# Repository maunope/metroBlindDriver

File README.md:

# Disclaimer
This is still a prototype; the circuit design was built and tested on a perfboard, the KiCad board design was never tested. Use at your own risk and plz **don't come whining if you damage stuff or set your house on fire.**

# WARNING
This project entails working with a 220V powered device with a metal chassis and **no grounding**. These devices are 40+ years old and saw lots of abuse; wire insulation may fail, and motor windings may short circuit. Before wiring anything up, check impedance between the chassis, the engine hull, and all contacts carrying 220V power; anything below 2 megaohms means insulation needs to be re-checked. 
Consider wiring the blind chassis to the ground line for additional safety.

# Metro Blinds Driver

Arduino-based driver board to control Acotral MA100 electric locomotives' front and side stops blinds.

Acotral MA100s were first issued to Rome's **"A"** metro line where they were in service between 1980 and 2005, before being overhauled/modified and reassigned to the Roma Lido line until their decommissioning in 2018. 

[Trasporti di Roma](https://romaatac.altervista.org/mezzi-di-roma/ma-100/)
[Wikipedia](https://it.wikipedia.org/wiki/Elettromotrici_ACOTRAL_MA_100)

Stops signaling blinds coming from wagon dismantling started circulating among flip clock collectors and have become a somewhat common find on online marketplaces.

Blinds are controlled through a 7-bit string identifying stops and are powered at 110V AC (motor) / 48V DC (control). This project emulates original locomotive control signals to drive them and display stops.

The board design in this project runs 5V DC control signals and 220V power; it requires minimal modifications to the original blinds' wiring. It is fairly easy, however, to adapt it to run 48V/110V to 100% preserve the integrity of the original wiring.

## Main features   
- Runs through stops using the blind's internal motor
- Allows manual stop selection or programmed stops sequence mode
- Allows saving configurations to the Arduino EEPROM
- Implements several controls to prevent damage/overheating in case of malfunctions

## Lateral blind design
The `LATERAL_BLIND` compile flag enables a command table built for smaller punched rollers found on side-mounted train blinds. This mode is intended to address blinds with smaller punched rollers, those mounted on the side of trains rather than the larger frontal rollers.

On the specimen I tested, the pinout was different compared to the larger frontal roller, but this may not always be true. If your roller is different, you may need to recreate the command array for your exact roller.

## Manual vs. Program mode

In **manual mode** (default), stops are selected through serial port commands or single button presses. The board LED is lit during Manual mode. 

**Program mode** automatically loops a sequence of stops, one step every hour by default. The program will be resumed from the last reached stop in case of power OFF/ON; the hourly step timer will be reset. The board LED is off during Program mode.

To switch between modes, either use serial commands or press the board button for **3 seconds**. 

## Dependencies

- EEPROM (comes with Arduino IDE)
- [Rocket Scream Low Power](https://github.com/rocketscream/Low-Power)

## Arduino circuit board

Check the schematic in this repo; I've built and tested it on perfboard. The board design might not be 100% correct, and the layout could definitely use some improvement.

**How to read LED signals**

Either for good or bad news, the Arduino board LED will flash. 

## Original electromechanical control logic 

A punched roller is used to encode 40 unique blind positions. When a string of bits is applied to the pinstripe, the motor spins until the holes combination under the pinstripe matches powered pins, i.e.:

- **0b00111000** bit string corresponding to Termini station is applied to the pinstripe, powering pins 4, 5, 6 from the left (1st left pin is common)
- **0b0011110** bit string on the control roller is under the pinstripe; current flows through pins 4, 5, 6, and the motor spins
- Next roller bit string is **0b0100110** on the control roller; current flows through pin 6, and the motor keeps spinning
- The roller bit string is now **0b11000111**; all 1s on the pinstripe match a 0 on the roller, no current flows, the motor **stops** and will remain still until a different bit string is selected.

The original control board has 7 control pins, 2 relay coil pins, and 2 motor power pins, exposed through a DIN 41622 male connector on the side or back panel.

The original wiring:
- Pin 1-6 and 12: stop selection bit string
- Pin 11: unwired
- Pin 10: 110V AC to relay interrupted line
- Pin 9: Relay coil (+48V signal from selection roller return line)
- Pin 8: Relay coil N
- Pin 7: 110V returning from motor

## Blind Board schematic and modifications

The blind board schematic is available in "metroBlindDriver blind board" KiCad design:

In the original blind design, 48V DC bits would be fed into pins 1-6 and 12; they would reach the control roller through diodes and would power the 48V relay coil through the roller common pin until the desired stop was reached. 

The original blind wiring can be easily modified to accept standard household 220V AC power and 5V DC signals.

**IMPORTANT**: Don't use this board design with 48V signals to avoid damage and fire hazard!

**IMPORTANT**: Don't run 220V AC through the motor before its coils are wired in series to avoid damage and fire hazard!

**220V AC motor wiring** Wire the motor as shown in the picture below to drive it with 220V AC power. Plastic motor caps on most (all?) blinds have diagrams explaining how to wire coils in series/parallel.

**5V DC external relay wiring**

To bypass the 48V coil and use an external relay, clip the motor **N** wire from the connector board trace (board end, not motor end!) and solder it to the top left pin on the DIN connector. If in doubt, use the only pin trace with no wires attached. 

Replacing the original 48V relay with a 5V or 12V one isn't sufficient, as the coil has a 4kohm resistor wired in series; plus, compatible relays are out of production, hard to source, and quite expensive. 

I wanted to preserve the original circuitry as much as possible, but definitely didn't want to faff with 48V signals.
I figured since I had already wired the motor for 220V AC, another small modification wouldn't matter much, and moving a wire to a different pin seemed way less invasive than replacing a relay and a big *ss resistor.
You might want to do things differently here; the circuit is easy enough to work with, these are just my 2c :-) 

Rewired schematic below:

The new wiring:
- Pin 1-6 and 12: 5V bit string
- Pin 11: to motor relay NO contact on Arduino board
- Pin 10: unwired, can be used to ground the blind chassis
- Pin 9: to Arduino "Any Running" pin
- Pin 8: unwired
- Pin 7: to motor relay NO contact on Arduino board

## How to install and adjust

**First things first, let's not fry stuff**

- Check wirings and voltages
- **Mandatory**: rewire the blind board to use an external 5V relay; **don't use 48V signals with this Arduino board design!**
- **Optional**: rewire the motor to run on 220V AC; if you happen to have a 110V AC power source, that will work fine
- Wire the DIN connector pins; be sure not to short circuit anything
- Power the board and the motor **L** wire
 **No smoke? Good.**

By default, the controller will wait for commands in manual mode with the board LED **ON**.

- Press the board button briefly; the blind should roll one stop forward
- (Optional) press the board button for 3 seconds to switch to Program mode

## Push buttons commands

- **Brief press:** move one stop forward
- **3 seconds press:** switch between Manual and Program mode

## Serial port commands

Commands format: **(<<|>>)[A-Z,0-9]+**

- **<<** to read info, **>>** to set
- Command name, in caps
- (Where applicable) parameters

One command per line; the parser is pretty crude, please stick to tested commands ;-) 

**Available commands**:

- **>>GO[0-9][0-9]** select stop by zero-padded two-digit number, 01-40 (only works in manual mode)
- **>>(stop name)** (i.e., >>ANAGNINA, >>CINECITTA) select stop by name (only works in manual mode)
- **>>STOP** halt the motor
- **>>RUN** continuously run the motor 
- **>>PROGRAMSTEPSSECONDS[0-9]{4}** write steps duration for program mode, zero-padded four digits
- **<<PROGRAMSTEPSSECONDS** read steps duration for program mode
- **>>DEFAULTPROGRAM** load the default stops program to memory
- **>>PROGRAMSTOPS[0-9][0-9](?:[0-9][0-9]){0,39}** write program mode stops sequence, zero terminated, up to 40 zero-padded two-digit positive integers. The sequence is required to be ascending (i.e., 1-2-3 valid, 1-3-2 not valid)
- **<<PROGRAMSTOPS** print the program stops sequence currently in memory
- **>>PROGRAMMODE** switch to Program mode
- **>>MANUALMODE** switch to Manual mode (default)
- **>>RESETDEFAULTS** reset default configuration 
- **<<EEPROMDATA** print current eeprom conf
- **>>EEPROMDATA** write current conf from ram to eeprom
- **<<POSITION** print the current blind roller position
- **<<COMPILEDATETIME** print the sketch build timestamp

## Build flags

-DEBUG_MODE enable serial port debug messages, disable sleep mode

## Unreachable stops

The control roller pinstripe 8 signals encode 40 unique bit strings, each with three raised bits (i.e., 0b11001000, 0b00110010). This allows moving from any stop to any other by applying the destination code bit string to stop selection pins. 

At least, this is how the control roller would work hadn't its original designers decided to leave the rightmost pin unwired.

As a result, 5 out of 40 stops are encoded by only 2 wired pins and only work when selected starting from the 13 stops right behind them. 
The matrix below highlights misencoded stops and the stops that would be wrongly displayed when their code is used, i.e.:

- The blind displays stop **2** (code **0b1000110**)
- Stop **21** (code **0b1100000**) is selected
- The blind spins until stop **6**, (code **0b1100001**)
- The bitwise "(input bit string) **AND NOT** (roller bit string)" of stops **21** and **6** codes is 0 -> the relay coil is not powered
- The blind stopped on stop **6** before reaching **21** and would halt on 26, 27, 30 and 37 due to the same reason
- (**Note:** code **0b1100000** correctly drives the blind to stop **21** starting from stops 7-20)

This behavior **did not** affect actual service on Roma Metro **A** as the 5 impacted stops were blank. I decided to leave it unchanged as an interesting quirk of the original design; you might want to fix it if you plan to display anything on stops 21-25 :-D 

## Troubleshooting

**Q:** I can't tell what's going on with EEPROM data.

**A:** The <<EEPROMDATA command can extract all the info saved on the EEPROM.

**Q:** I keep getting "nonexistent stop" error.

**A:** Check wiring; any short circuit? Any missing wire? 

**Q:** Motor buzzes and doesn't spin! What's wrong?

**A:** Have you rewired the motor correctly? 

**Q:** I rebooted the board, and all my configurations are lost.

**A:** Run >>EEPROMDATA to persist configuration on EEPROM.

**Q:** I have disassembled the punched roller and now it doesn't stop on the right positions.

**A:** If the roller is misaligned, it will not work correctly. The solution is to disassemble it again, align it to the right stop, and reassemble it. It is possible to fine tune it by undoing the screw on the roller side and moving the outer plate slightly.

**Q:** That PCB design is **lame**!

**A:** It is. Any help much appreciated! ;-)

## Todo
- Readme completion
- Circuit board layout improvement

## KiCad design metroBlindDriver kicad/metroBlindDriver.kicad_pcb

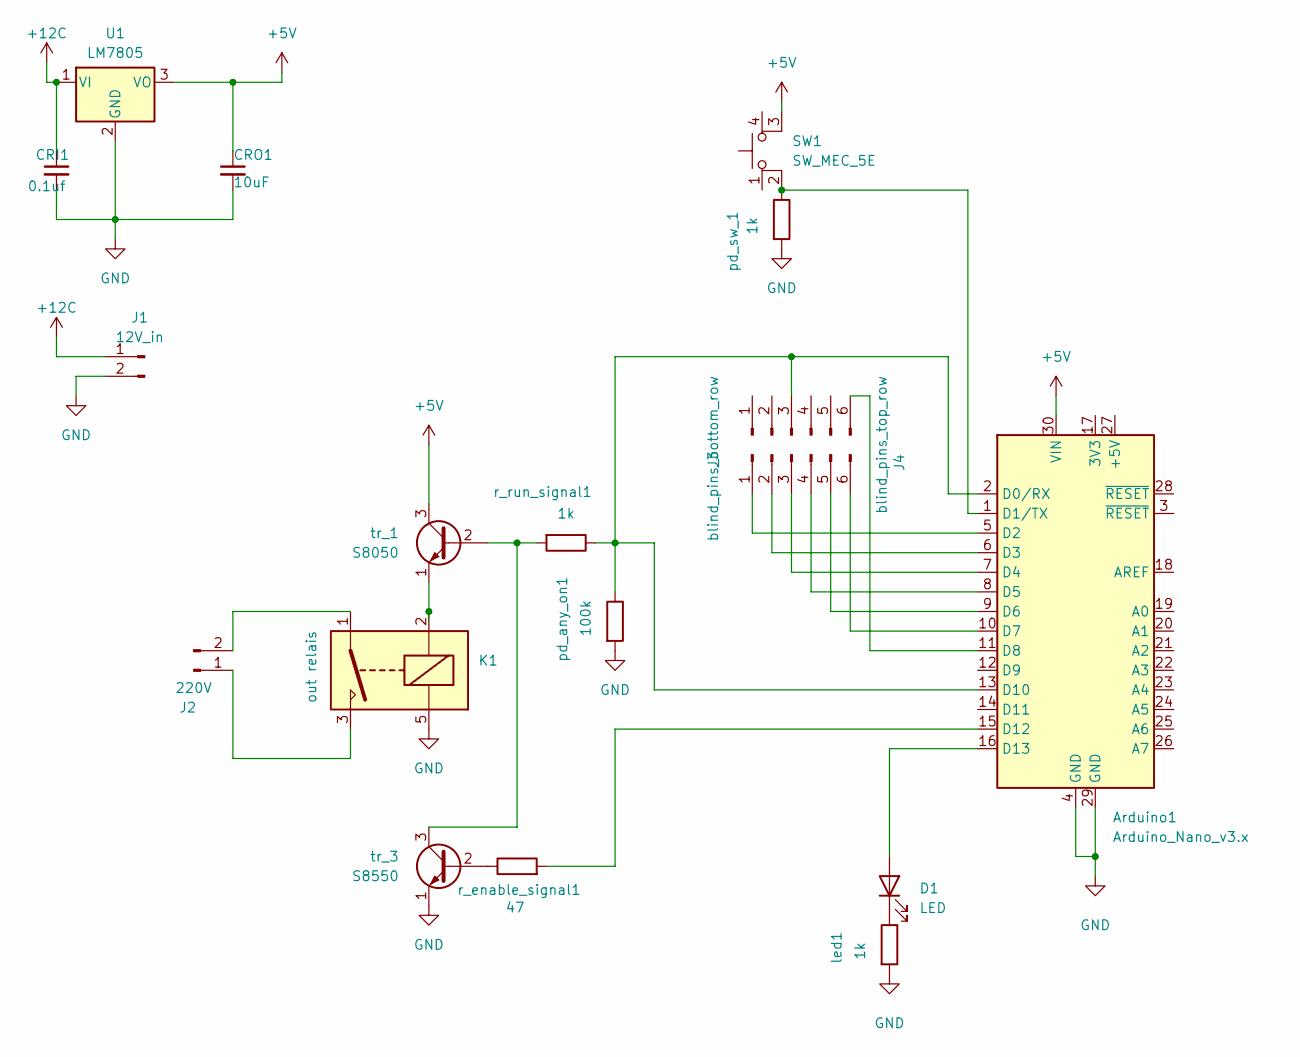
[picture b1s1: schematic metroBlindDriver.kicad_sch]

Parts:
Arduino1: Arduino_Nano_v3.x; Arduino_Nano
CRI1: 0.1uf; C_Disc_D5.1mm_W3.2mm_P5.00mm
CRO1: 10uF; C_Disc_D5.1mm_W3.2mm_P5.00mm
D1: LED; LED_D3.0mm
J1: 12V_in; SolderWire-1sqmm_1x02_P5.4mm_D1.4mm_OD2.7mm
J2: 220V; SolderWire-1sqmm_1x02_P5.4mm_D1.4mm_OD2.7mm
J3: blind_pins_bottom_row; PinHeader_1x06_P2.00mm_Vertical
J4: blind_pins_top_row; PinHeader_1x06_P2.00mm_Vertical
K1: out relais; Relay_SPST_SANYOU_SRD_Series_Form_A
SW1: SW_MEC_5E; SW_Push_2P1T_Toggle_CK_PVA1xxH1xxxxxxV2
U1: LM7805; TO-220-3_Vertical
led1: 1k; R_Axial_DIN0207_L6.3mm_D2.5mm_P7.62mm_Horizontal
pd_any_on1: 100k; R_Axial_DIN0207_L6.3mm_D2.5mm_P7.62mm_Horizontal
pd_sw_1: 1k; R_Axial_DIN0207_L6.3mm_D2.5mm_P7.62mm_Horizontal
r_enable_signal1: 47; R_Axial_DIN0207_L6.3mm_D2.5mm_P7.62mm_Horizontal
r_run_signal1: 1k; R_Axial_DIN0207_L6.3mm_D2.5mm_P7.62mm_Horizontal
tr_1: S8050; TO-92_Inline
tr_3: S8550; TO-92_Inline

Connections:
+5V: Arduino1.30 (VIN), CRO1.1, SW1.3 (K), U1.3 (VO), tr_1.3 (C)
+12C: CRI1.1, J1.1, U1.1 (VI)
GND: Arduino1.4 (GND), Arduino1.29 (GND), CRI1.2, CRO1.2, J1.2, K1.5, U1.2 (GND), led1.2, pd_any_on1.2, pd_sw_1.2, tr_3.1 (E)
unnamed: Arduino1.2 (D0/RX), Arduino1.13 (D10), J4.3, pd_any_on1.1, r_run_signal1.1
unnamed: Arduino1.1 (D1/TX), SW1.2, pd_sw_1.1
unnamed: Arduino1.5 (D2), J3.1
unnamed: Arduino1.6 (D3), J3.2
unnamed: Arduino1.7 (D4), J3.3
unnamed: Arduino1.8 (D5), J3.4
unnamed: Arduino1.9 (D6), J3.5
unnamed: Arduino1.10 (D7), J3.6
unnamed: Arduino1.11 (D8), J4.6
unnamed: Arduino1.15 (D12), r_enable_signal1.2
unnamed: Arduino1.16 (D13), D1.2 (A)
unnamed: D1.1 (K), led1.1
unnamed: J2.1, K1.3
unnamed: J2.2, K1.1
unnamed: r_run_signal1.2, tr_1.2 (B), tr_3.3 (C)
unnamed: K1.2, tr_1.1 (E)
unnamed: r_enable_signal1.1, tr_3.2 (B)

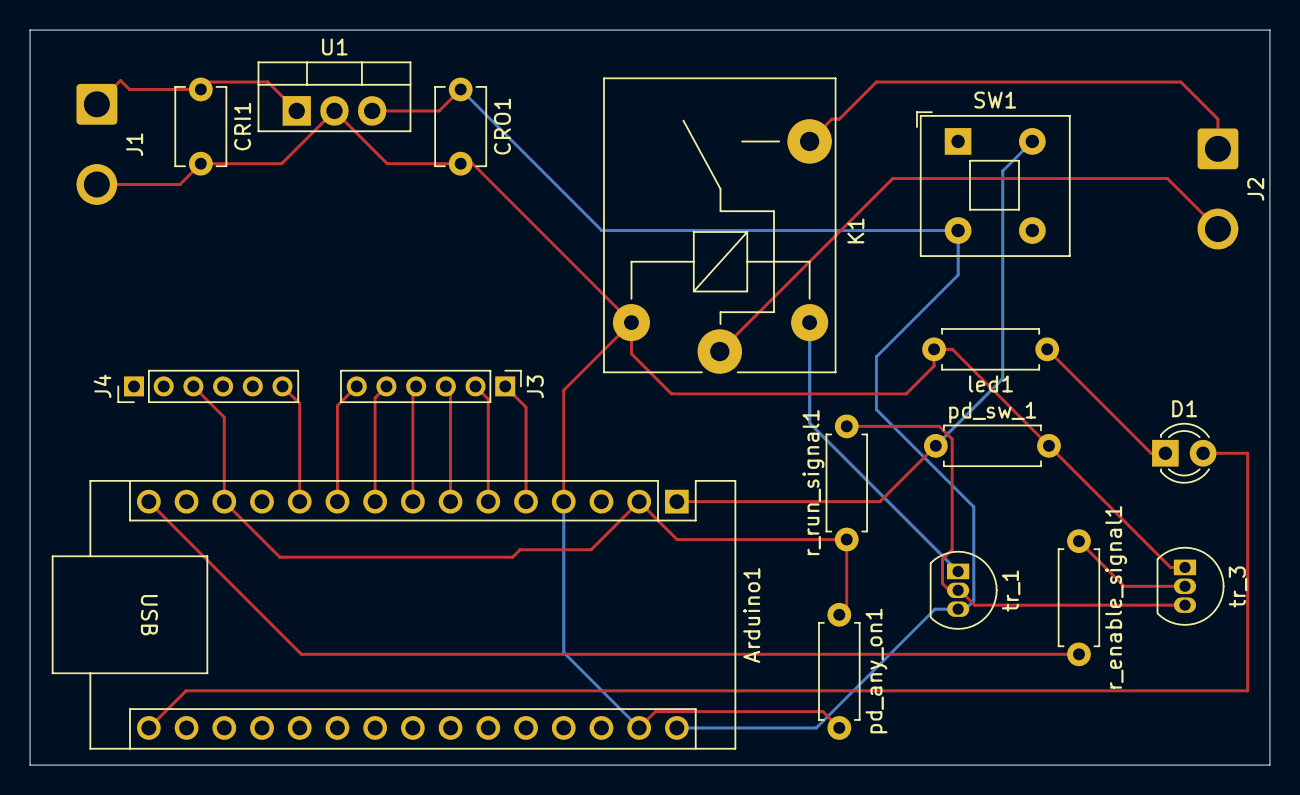
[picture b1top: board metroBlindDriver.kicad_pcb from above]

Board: 2 copper layers, 83.5 x 49.5 mm, 18 parts (0 on the bottom side), 20 nets.

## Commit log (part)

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2025-01-30 first readme
2025-01-31 added several functions, initial bulk edits
2025-01-31 gitignore
2025-01-31 manual and program mode working
2025-01-31 debug mode strings
2025-02-01 refactored code, added continuous runtime protection
2025-02-01 updated doc
2025-02-01 fix to program mode and doc
2025-02-01 documentation update
2025-02-01 various doc edits
2025-02-01 fix image
2025-02-09 - configuration persistence - switch to program mode strings for debug - debug mode write to serial - methods for saving program, mode, program step interval
2025-02-09 fixed stops overlaps image
2025-02-09 resized images
2025-02-10 added push button commands
2025-02-13 - Added idle mode - Fixed feedback led leaving led in wrong position - Fixed shared buffer for bitstring output bug - Added check to avoid stops programs going backwards - Added <<EEPROMDATA - fixed 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
2025-02-14 updated pcb design
2025-02-14 added board layout image
2025-02-18 added schematics to readme
2025-02-18 updates to readme
2025-02-18 led error codes
2025-02-18 fixed led error code
2025-02-21 fixed readme, added sch file
2025-03-13 fixed bug on sleep mode that put the board to sleep every 5 minutes, implemented reset defaults method, corrected a bug that rewrote conf to eeprom on each setup, implemented serial command to read c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
2025-03-16 fixed a bug on idle mode
2025-03-16 further correction to sleep mode
2025-03-18 added recovery from unknown positin in program mode
2026-03-24 doc typos&stuff
2026-03-24 fixed typo in serial commands manual
